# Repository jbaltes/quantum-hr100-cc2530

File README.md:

# About

quantum-hr100-cc2530 - fan controller board with mains power and zigbee

quantum-hr100-cc2530 is a open source hardware board.
It can controls pendulum fan Quantum HR 100 over zigbee.

# Warning

This project uses dangerous mains voltage. Be carefull.

## Structure

 * Terminal blocks for input power, fan supply and pwm signal
 * non isolated ACDC power supply
 * cc2530 rf-module
 * switchable fan supply with triac
 * cc2530 programming connector
 * i2c connector for e.g. temperature/humidity sensor

## Quantum HR 100

The pendulum fan Quantum HR 100 from aerauliqa has a two direction fan motor with pwm control unit.

The original pwm control works with 10Hz. A duty cycle of 50% stops the motor from running.
Maximum tested pwm frequency with 50% duty cylce to stop the motor was 400Hz.

The pwm input circuit of the motor clamps the voltage to 2.65V with about 5mA current at 3.3V supply voltage.

The pwm control voltage threshols are:
on-threshold: 2.0V
off-threshold: 1.0V

The pwm duty cycle thresholds are:
<= 43% on
>= 47% off
<= 53% off
>= 57% on

PWM frequency of 4Hz, 8Hz, 15Hz didn't work. 30Hz works fine.

## cc2530

CC2530 SZ1V5 module
30x20x4mm pitch 1.25mm

GND   1    24 RST#
GND   2    23 P0_0
3V3   3    22 P0_1
3V3   4    21 P0_2
P2_2  5    20 P0_3
P2_1  6    19 P0_4
P2_0  7    18 P0_5
P1_7  8    17 P0_6
P1_6  9    16 P0_7
P1_5 10    15 P1_0
P1_4 11    14 P1_1
P1_3 12    13 P1_2

A working configurable firmware for the zigbee module can be found at:
github.com/ptvoinfo/zigbee-configurable-firmware

## programming cc2530

### Raspberry Pi 1B

www.zigbee2mqtt.io/guide/adapters/flashing/alternative_flashing_methods.html

Rasphberry Pi need wiringPi (apt install wiringPi) - includes command gpio: "gpio readall" shows physical connector pins to wiring number mapping (wPi)

physical pin 13 -> wPi 2 (clock) -> DEBUG_CLK (DC) cc2530_P2_2
physical pin 15 -> wPi 3 (data) -> DEBUG_DATA (DD) cc2530_P2_1
physical pin 18 -> wPI 5 (reset) -> cc2530_RST#

 * read chip ID: cc_chipid -c 2 -d 3 -r 5
 * read firmware: cc_read -c 2 -d 3 -r 5
 * write firemware: cc_write -c 2 -d 3 -r 5 <firmware-hex-file>

### USB programmer

2x5 pin header assignment:
GND  1  2 VDD (3V3)
DC   3  4 DD
CS#  5  6 SCLK
RST# 7  8 MOSI
VDD  9 10 MISO

# License

The hardware is licensed under CERN OHL v.1.2. See COPYING.hardware for the complete license.

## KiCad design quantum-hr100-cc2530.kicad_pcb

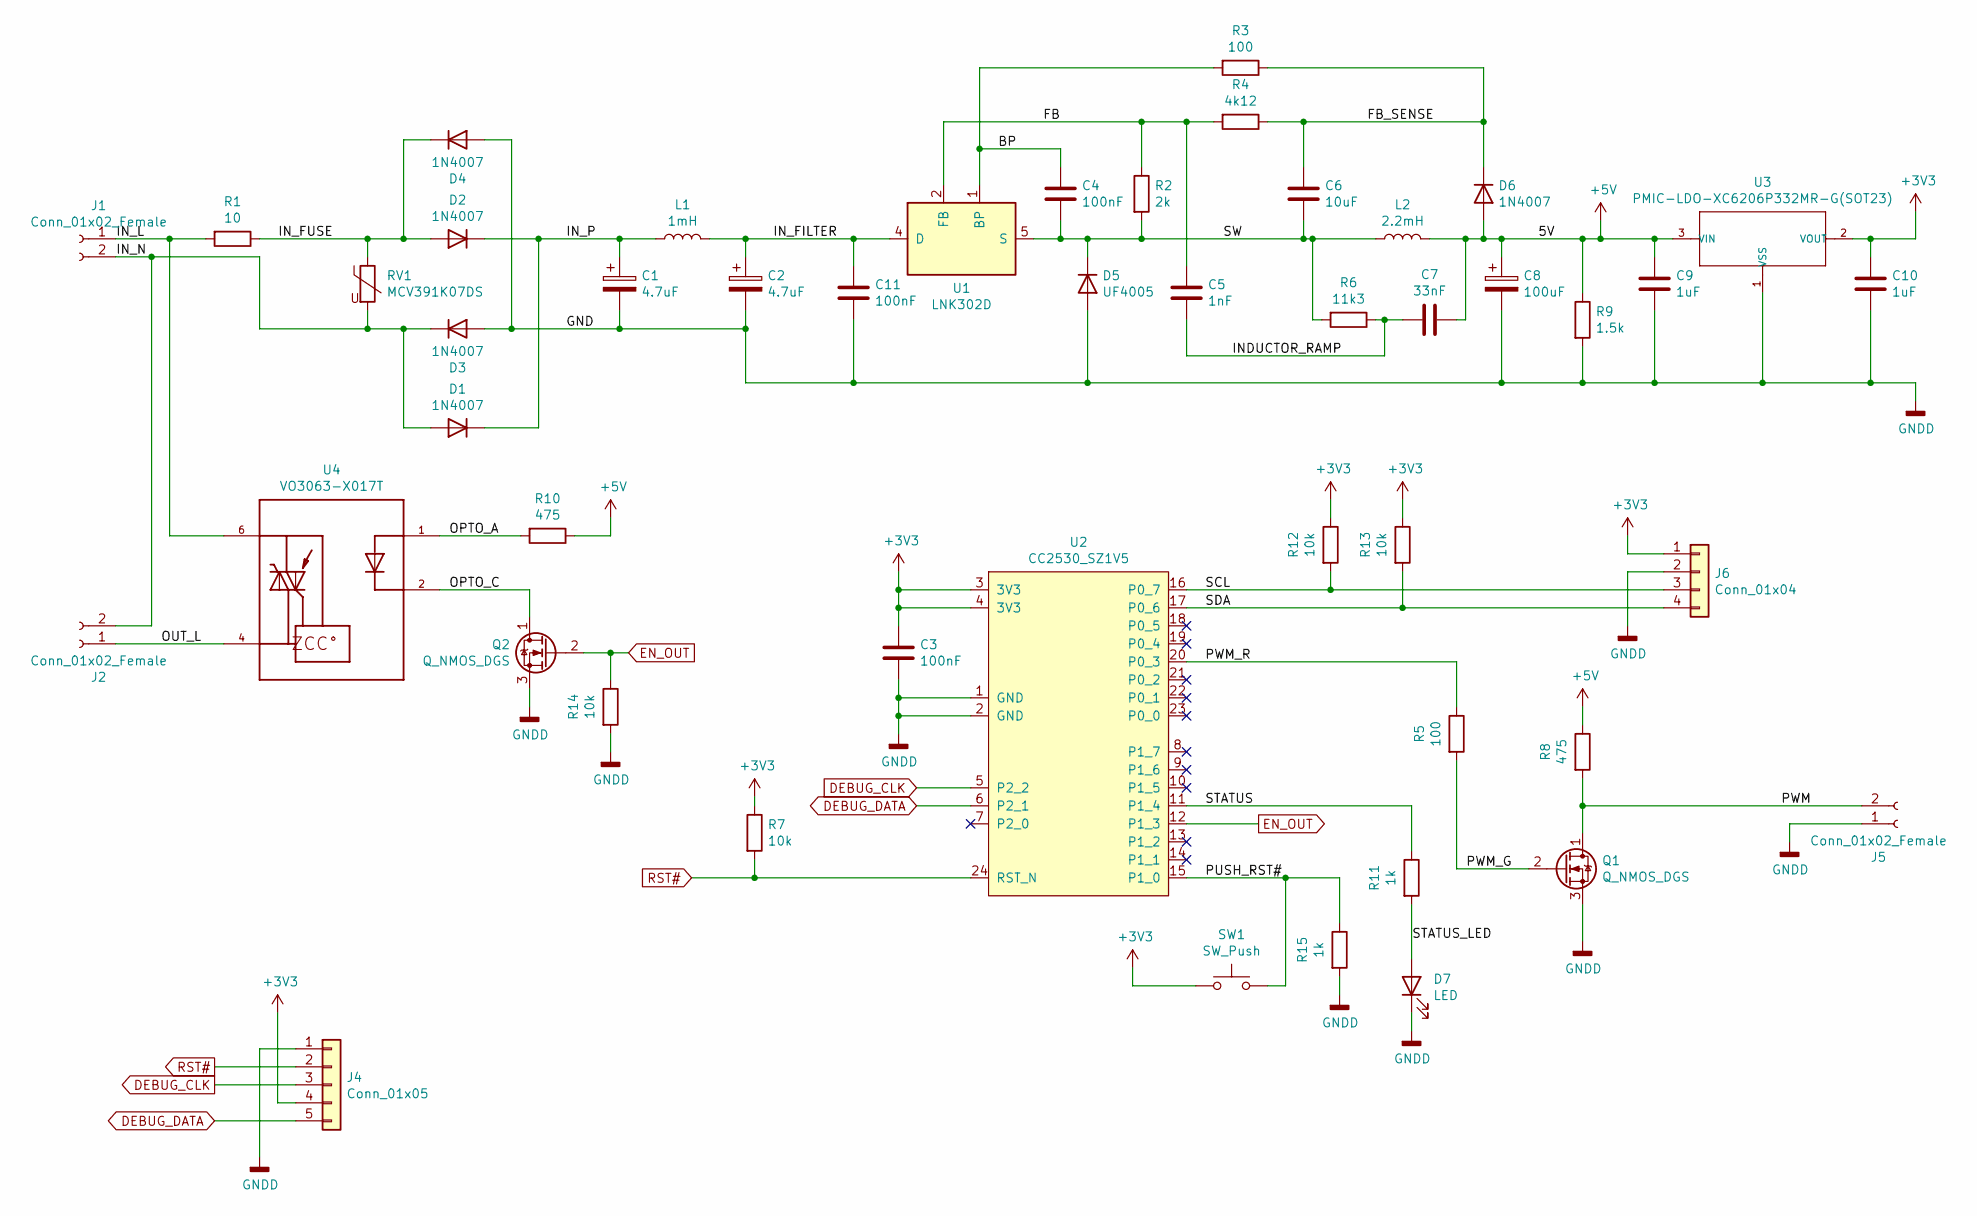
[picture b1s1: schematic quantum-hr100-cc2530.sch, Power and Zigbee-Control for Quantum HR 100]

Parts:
C1, C2: 4.7uF; CP_Radial_D10.0mm_P5.00mm
C3: 100nF; C_0603_1608Metric
C4: 100nF; C_1206_3216Metric_Pad1.33x1.80mm_HandSolder
C5: 1nF; C_0603_1608Metric_Pad1.05x0.95mm_HandSolder
C6: 10uF; C_1206_3216Metric_Pad1.33x1.80mm_HandSolder
C7: 33nF; C_0603_1608Metric_Pad1.05x0.95mm_HandSolder
C8: 100uF; CP_Radial_D5.0mm_P2.00mm
C9, C10: 1uF; C_0603_1608Metric
C11: 100nF; C_1210_3225Metric_Pad1.33x2.70mm_HandSolder
D1, D2, D3, D4, D6: 1N4007; D_SMA
D5: UF4005; D_SMA
D7: LED; LED_0603_1608Metric_Pad1.05x0.95mm_HandSolder
J1, J2, J5: Conn_01x02_Female; P-250-202
J4: Conn_01x05; PinHeader_1x05_P1.27mm_Vertical
J6: Conn_01x04; Molex_PicoBlade_53047-0410_1x04_P1.25mm_Vertical
L1: 1mH; L_Axial_L11.0mm_D4.5mm_P5.08mm_Vertical_Fastron_MECC
L2: 2.2mH; L_Radial_D9.5mm_P5.00mm_Fastron_07HVP
Q1, Q2: Q_NMOS_DGS; SOT-23
R1: 10; R_Axial_DIN0414_L11.9mm_D4.5mm_P5.08mm_Vertical
R2: 2k; R_1206_3216Metric_Pad1.30x1.75mm_HandSolder
R3: 100; R_0603_1608Metric_Pad1.05x0.95mm_HandSolder
R4: 4k12; R_0603_1608Metric_Pad1.05x0.95mm_HandSolder
R5: 100; R_1206_3216Metric_Pad1.30x1.75mm_HandSolder
R6: 11k3; R_1206_3216Metric_Pad1.30x1.75mm_HandSolder
R7: 10k; R_0603_1608Metric_Pad1.05x0.95mm_HandSolder
R8, R10: 475; R_0603_1608Metric_Pad0.98x0.95mm_HandSolder
R9: 1.5k; R_0603_1608Metric_Pad0.98x0.95mm_HandSolder
R11, R15: 1k; R_0603_1608Metric_Pad0.98x0.95mm_HandSolder
R12, R13, R14: 10k; R_0603_1608Metric_Pad0.98x0.95mm_HandSolder
RV1: MCV391K07DS; RV_Disc_D9mm_W5.7mm_P5mm
SW1: SW_Push; SW_PUSH_6mm_H13mm
U1: LNK302D; PowerIntegrations_SMD-8B
U2: CC2530_SZ1V5; CC2530_SZ1V5_HOLES
U3: PMIC-LDO-XC6206P332MR-G(SOT23); SOT-23; MPN XC6206P332MR-G
U4: VO3063-X017T; SOIC254P1030X460-6N

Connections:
+3V3: C3.1, C10.1, J4.4, J6.1, R7.1, R12.1, R13.1, SW1.1, U2.3 (3V3), U2.4 (3V3), U3.2 (VOUT)
+5V: C7.2, C8.1, C9.1, D6.2 (A), L2.2, R8.1, R9.1, R10.1, U3.3 (VIN)
/BP: C4.1, R3.2, U1.1 (BP)
/FB: C5.1, R2.1, R4.2, U1.2 (FB)
/FB_SENSE: C6.1, D6.1 (K), R3.1, R4.1
/INDUCTOR_RAMP: C5.2, C7.1, R6.1
/IN_FILTER: C2.1, C11.1, L1.2, U1.4 (D)
/IN_FUSE: D2.2 (A), D4.1 (K), R1.1, RV1.1
/IN_L: J1.1, R1.2, U4.6
/IN_N: D1.2 (A), D3.1 (K), J1.2, J2.2, RV1.2
/IN_P: C1.1, D1.1 (K), D2.1 (K), L1.1
/OPTO_A: R10.2, U4.1
/OPTO_C: Q2.1 (D), U4.2
/OUT_L: J2.1, U4.4
/PUSH_RST#: R15.1, SW1.2, U2.15 (P1_0)
/PWM: J5.2, Q1.1 (D), R8.2
/PWM_G: Q1.2 (G), R5.2
/PWM_R: R5.1, U2.20 (P0_3)
/SCL: J6.3, R12.2, U2.16 (P0_7)
/SDA: J6.4, R13.2, U2.17 (P0_6)
/STATUS: R11.1, U2.11 (P1_4)
/STATUS_LED: D7.2 (A), R11.2
/SW: C4.2, C6.2, D5.1 (K), L2.1, R2.2, R6.2, U1.5 (S), U1.6 (S), U1.7 (S), U1.8 (S)
DEBUG_CLK: J4.3, U2.5 (P2_2)
DEBUG_DATA: J4.5, U2.6 (P2_1)
EN_OUT: Q2.2 (G), R14.1, U2.12 (P1_3)
GNDD: C1.2, C2.2, C3.2, C8.2, C9.2, C10.2, C11.2, D3.2 (A), D4.2 (A), D5.2 (A), D7.1 (K), J4.1, J5.1, J6.2, Q1.3 (S), Q2.3 (S), R9.2, R14.2, R15.2, U2.1 (GND), U2.2 (GND), U3.1 (VSS)
RST#: J4.2, R7.2, U2.24 (RST_N)

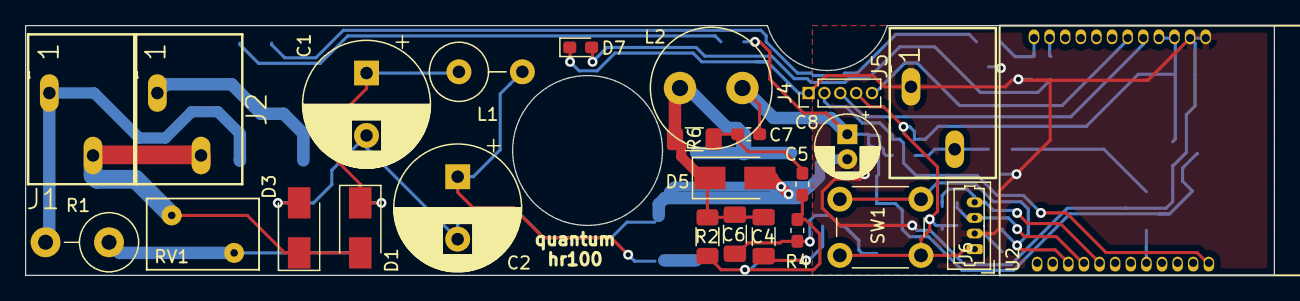
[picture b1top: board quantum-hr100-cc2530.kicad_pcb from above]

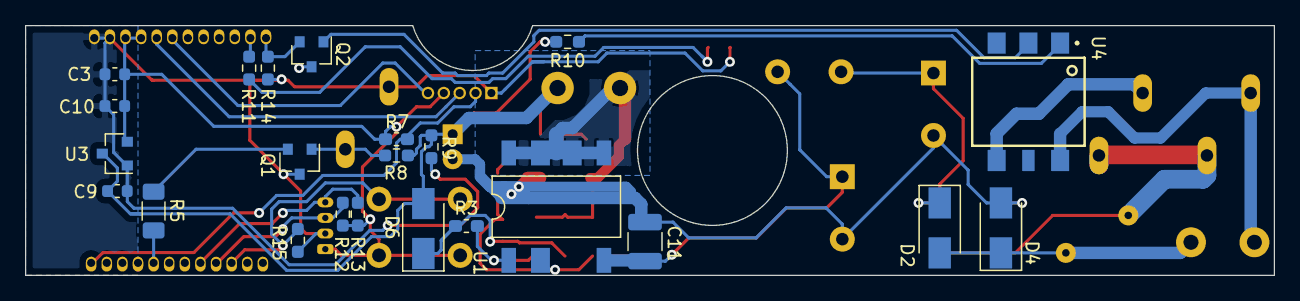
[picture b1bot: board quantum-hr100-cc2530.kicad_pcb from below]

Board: 2 copper layers, 100.0 x 20.0 mm, 48 parts (23 on the bottom side), 28 nets.

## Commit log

2022-07-09 add initial version - schematics and layout
2022-07-09 add license
